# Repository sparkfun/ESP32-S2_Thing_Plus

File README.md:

SparkFun ESP32-S2 Thing Plus
========================================

[*SparkFun ESP32-S2 Thing Plus (WRL-17381)*](https://www.sparkfun.com/products/17743)

The [SparkFun ESP32-S2 Thing Plus](https://www.sparkfun.com/products/17743) is a comprehensive development platform for [Espressif's ESP32](https://espressif.com/en/products/hardware/esp32/overview). This board has the ESP32-S2-WROOM (4MB) version of the module. The new ESP32-S2 module addresses the [security flaws](https://www.espressif.com/en/news/ESP32_FIA_Analysis) in the original ESP32. While the ESP32-S2 does include improved security features, it lacks the Bluetooth capabilities of the original ESP32 module. The ESP32-S2 Thing Plus includes a Qwiic adapter, LiPo battery JST connector, and 21 I/O pins.

Repository Contents
-------------------

* **/Hardware** - Eagle design files (.brd, .sch)
* **/Hardware/Production** - Production panel files (gerbers, .brd)

Documentation
--------------
* **[Hookup Guide](https://learn.sparkfun.com/tutorials/1660)** - Basic hookup guide for the ESP32-S2 Thing Plus.
* **[SparkFun Graphical Datasheets](https://github.com/sparkfun/Graphical_Datasheets)** -Graphical Datasheets for various SparkFun products.

Product Versions
----------------
* [WRL-17743](https://www.sparkfun.com/products/17743)- v1.0, Initial Release

License Information
-------------------

This product is _**open source**_! 

Please review the LICENSE.md file for license information. 

If you have any questions or concerns on licensing, please contact technical support on our [SparkFun forums](https://forum.sparkfun.com/viewforum.php?f=152).

Distributed as-is; no warranty is given.

- Your friends at SparkFun.

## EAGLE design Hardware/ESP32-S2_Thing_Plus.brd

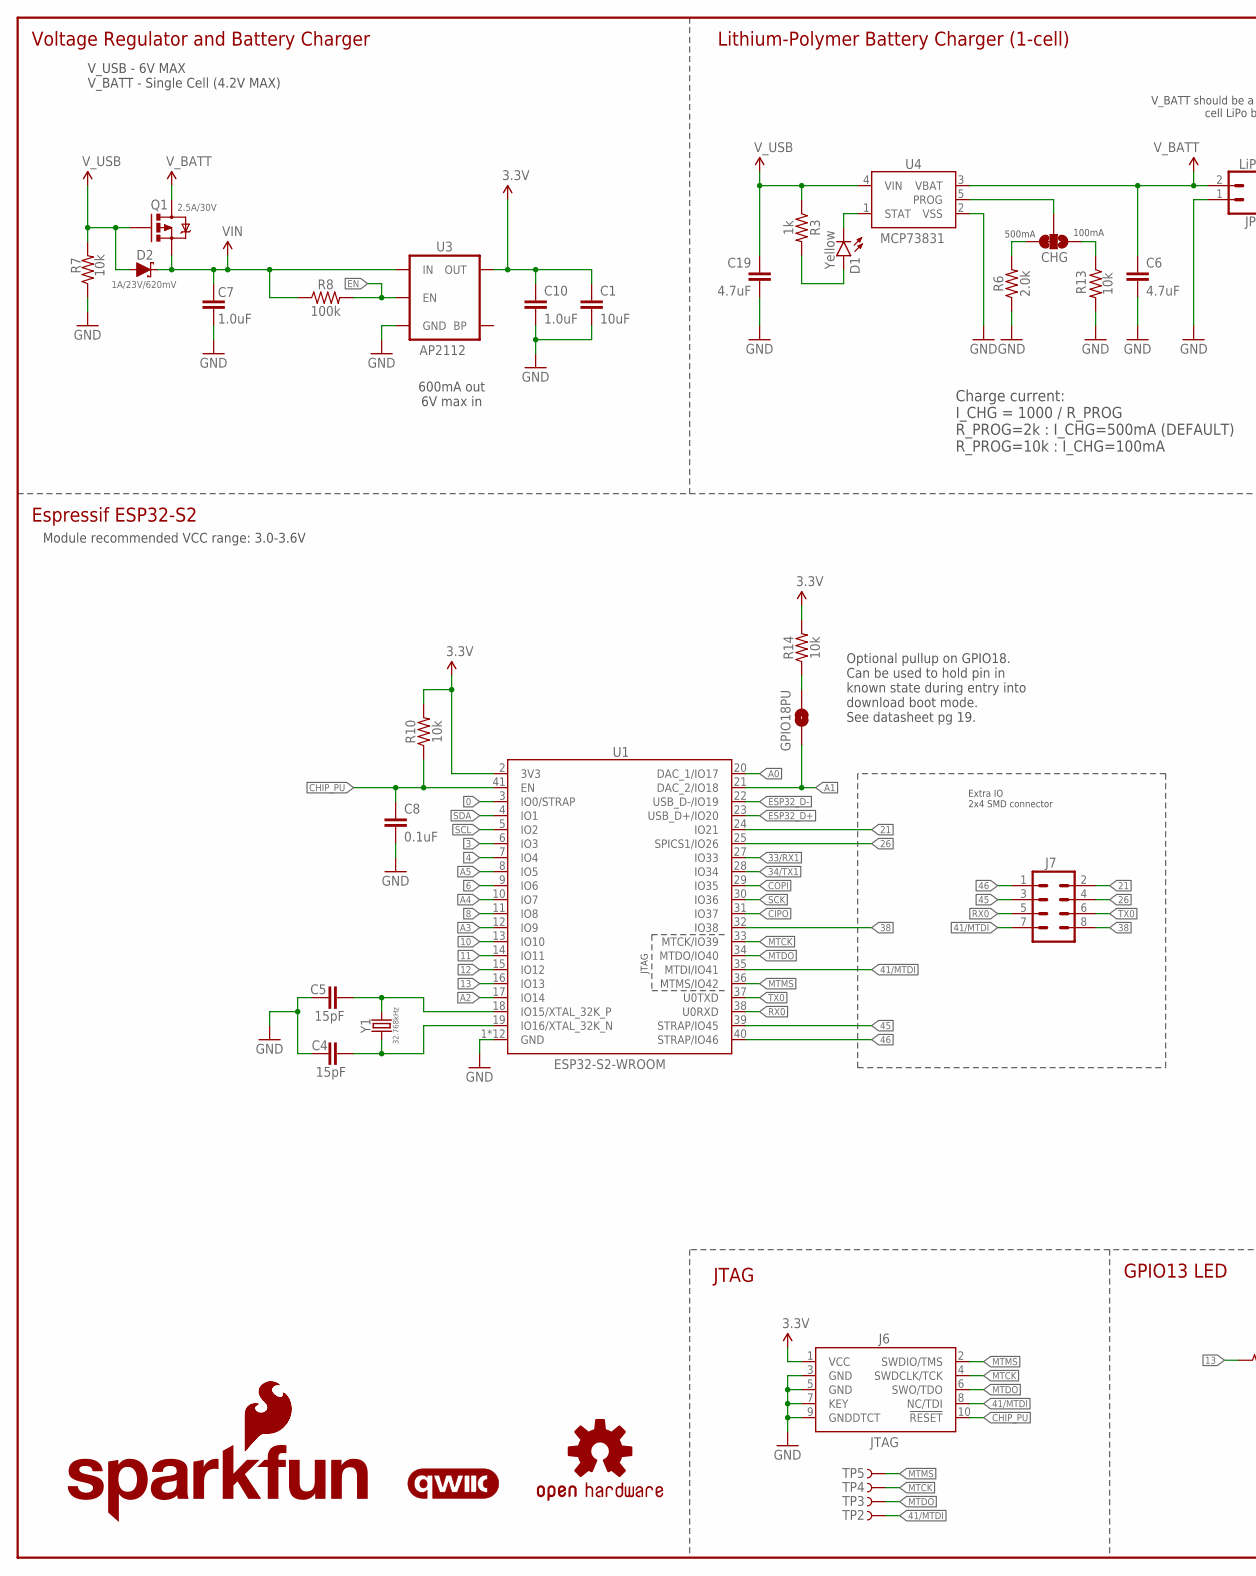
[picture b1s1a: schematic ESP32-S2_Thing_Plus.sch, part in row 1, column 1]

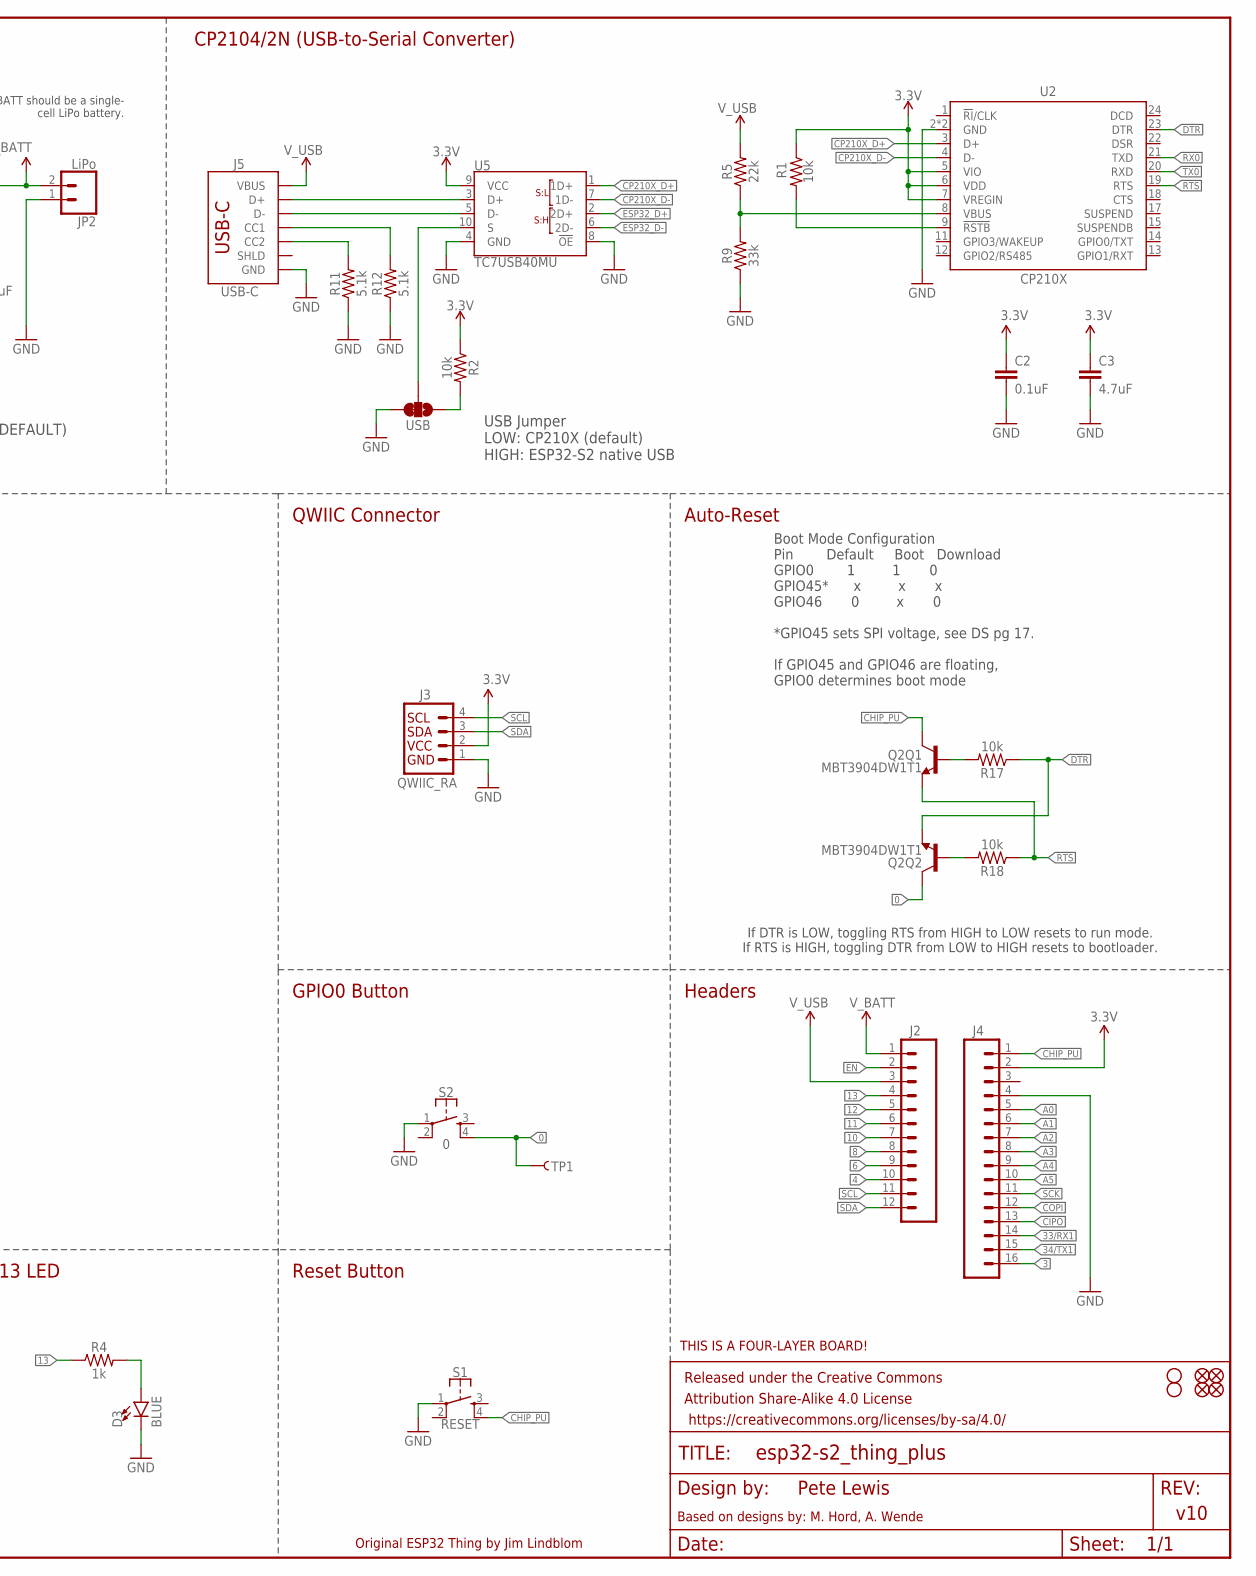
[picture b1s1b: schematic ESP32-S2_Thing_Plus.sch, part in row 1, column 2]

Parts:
C1: 10uF; 0402-TIGHT
C2, C8: 0.1uF; 0402-TIGHT
C3, C6, C19: 4.7uF; 0402-TIGHT
C4, C5: 15pF; 0402-TIGHT
C7, C10: 1.0uF; 0402-TIGHT
CHG: JUMPER-SMT_3_1-NC_TRACE_SILK; SMT-JUMPER_3_1-NC_TRACE_SILK
D1: Yellow; LED-0603
D2: 1A/23V/620mV; SOD-323
D3: BLUE; LED-0603
FD1, FD2, FD3, FD4: FIDUCIALUFIDUCIAL; FIDUCIAL-MICRO
FRAME1: FRAME-LEDGER; CREATIVE_COMMONS
GPIO18PU: JUMPER-SMT_2_NO_SILK; SMT-JUMPER_2_NO_SILK
H1, H2: STAND-OFF
J2: CONN_12SM_SQ_NO_SILK; 1X12_SM_SQ_NOSILK
J3: QWIIC_RA; JST04_1MM_RA
J4: CONN_161X16_SM_SQ_NOSILK; 1X16_SM_SQ_NOSILK
J5: USB-C; USB-C-16P-4LAYER-ISOLATED
J6: JTAG; 2X5-PTH-1.27MM-NO_SILK
J7: CONN_04X2_SMT_NO_POSTS_NS; 2X4_SMT_NO_POSTS_NS
JP2: LiPo; JST-2-SMD
LOGO1: SFE_LOGO_FLAME.1_INCH; SFE_LOGO_FLAME_.1
LOGO2: OSHW-LOGOMINI; OSHW-LOGO-MINI
LOGO3: SFE_LOGO_NAME_FLAME.1_INCH; SFE_LOGO_NAME_FLAME_.1
LOGO4: FOUR_LAYER_WARNING
LOGO6: QWIIC_LOGO_4MM; QWIIC_4MM
Q1: 2.5A/30V; SOT23-3@1
Q2: MBT3904DW1T1; SC70-6
R1, R2, R7, R10, R13, R14, R17, R18: 10k; 0402-TIGHT
R3, R4: 1k; 0402-TIGHT
R5: 22k; 0402-TIGHT
R6: 2.0k; 0603
R8: 100k; 0402-TIGHT
R9: 33k; 0402-TIGHT
R11, R12: 5.1k; 0402-TIGHT
S1: RESET; TACTILE_SWITCH_SMD_4.6X2.8MM
S2: 0; TACTILE_SWITCH_SMD_4.6X2.8MM
TP1: TEST-POINTTP_15TH_THRU; TP_15TH
TP2, TP3, TP4, TP5: TEST-POINT3X4; PAD.03X.04
U1: ESP32-S2-WROOM
U2: CP210X; QFN24
U3: AP2112; SOT23-5
U4: MCP73831; SOT23-5
U5: TC7USB40MU; UQFN10
USB: JUMPER-SMT_3_1-NC_TRACE_SILK; SMT-JUMPER_3_1-NC_TRACE_SILK
Y1: 32.768kHz; CRYSTAL-SMD-3.2X1.5MM

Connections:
0: Q2.6 (C), S2.4, TP1.P$1, U1.3 (IO0/STRAP)
3: J4.16, U1.6 (IO3)
3.3V: C1.1, C2.1, C3.1, C10.1, J3.2, J4.2, J6.1 (VCC), R1.1, R2.1, R10.2, R14.2, U1.2 (3V3), U2.5 (VIO), U2.6 (VDD), U2.7 (VREGIN), U3.5 (OUT), U5.9 (VCC)
4: J2.10, U1.7 (IO4)
6: J2.9, U1.9 (IO6)
8: J2.8, U1.11 (IO8)
10: J2.7, U1.13 (IO10)
11: J2.6, U1.14 (IO11)
12: J2.5, U1.15 (IO12)
13: J2.4, R4.1, U1.16 (IO13)
21: J7.2, U1.24 (IO21)
26: J7.4, U1.25 (SPICS1/IO26)
33/RX1: J4.14, U1.27 (IO33)
34/TX1: J4.15, U1.28 (IO34)
38: J7.8, U1.32 (IO38)
41/MTDI: J6.8 (NC/TDI), J7.7, TP2.P$1, U1.35 (MTDI/IO41)
45: J7.3, U1.39 (STRAP/IO45)
46: J7.1, U1.40 (STRAP/IO46)
A0: J4.5, U1.20 (DAC_1/IO17)
A1: GPIO18PU.1, J4.6, U1.21 (DAC_2/IO18)
A2: J4.7, U1.17 (IO14)
A3: J4.8, U1.12 (IO9)
A4: J4.9, U1.10 (IO7)
A5: J4.10, U1.8 (IO5)
CC1: J5.A5 (CC1), R12.2
CC2: J5.B5 (CC2), R11.2
CHG: D1.C, U4.1 (STAT)
CHIP_PU: C8.1, J4.1, J6.10 (!RESET), Q2.3 (C), R10.1, S1.4, U1.41 (EN)
CIPO: J4.13, U1.31 (IO37)
COPI: J4.12, U1.29 (IO35)
CP210X_D+: U2.3 (D+), U5.1 (1D+)
CP210X_D-: U2.4 (D-), U5.7 (1D-)
DTR: Q2.1 (E), R17.1, U2.23 (DTR)
EN: J2.2, R8.2, U3.3 (EN)
ESP32_D+: U1.23 (USB_D+/IO20), U5.2 (2D+)
ESP32_D-: U1.22 (USB_D-/IO19), U5.6 (2D-)
GND: C1.2, C2.2, C3.2, C4.1, C5.1, C6.2, C7.2, C8.2, C10.2, C19.2, D3.C, J3.1, J4.4, J5.GND, J5.GND2 (GND), J6.3 (GND), J6.5 (GND), J6.7 (KEY), J6.9 (GNDDTCT), JP2.1 (2), R6.1, R7.1, R9.1, R11.1, R12.1, R13.2, S1.1, S2.1, U1.1 (GND), U1.26 (GND), U1.42 (GND), U1.GNDEP0 (GND), U1.GNDEP1 (GND), U1.GNDEP2 (GND), U1.GNDEP3 (GND), U1.GNDEP4 (GND), U1.GNDEP5 (GND), U1.GNDEP6 (GND), U1.GNDEP7 (GND), U1.GNDEP8 (GND), U2.2 (GND), U2.PAD (GND), U3.2 (GND), U4.2 (VSS), U5.4 (GND), U5.8 (!OE!), USB.3
MTCK: J6.4 (SWDCLK/TCK), TP4.P$1, U1.33 (MTCK/IO39)
MTDO: J6.6 (SWO/TDO), TP3.P$1, U1.34 (MTDO/IO40)
MTMS: J6.2 (SWDIO/TMS), TP5.P$1, U1.36 (MTMS/IO42)
unnamed: R1.2, U2.9 (!RSTB)
unnamed: D3.A, R4.2
unnamed: J5.A6 (D+), J5.B6 (D+), U5.3 (D+)
unnamed: R5.1, R9.2, U2.8 (VBUS)
unnamed: J5.A7 (D-), J5.B7 (D-), U5.5 (D-)
unnamed: R2.2, USB.1
unnamed: C5.2, U1.18 (IO15/XTAL_32K_P), Y1.P$2 (2)
unnamed: C4.2, U1.19 (IO16/XTAL_32K_N), Y1.P$1 (1)
unnamed: CHG.2, U4.5 (PROG)
unnamed: Q2.5 (B), R17.2
unnamed: CHG.1, R13.1
unnamed: Q2.2 (B), R18.2
unnamed: CHG.3, R6.2
unnamed: GPIO18PU.2, R14.1
unnamed: D1.A, R3.2
RTS: Q2.4 (E), R18.1, U2.19 (RTS)
RX0: J7.5, U1.38 (U0RXD), U2.21 (TXD)
SCK: J4.11, U1.30 (IO36)
SCL: J2.11, J3.4, U1.5 (IO2)
SDA: J2.12, J3.3, U1.4 (IO1)
TX0: J7.6, U1.37 (U0TXD), U2.20 (RXD)
USB_SEL: U5.10 (S), USB.2
VIN: C7.1, D2.C, Q1.2 (S), R8.1, U3.1 (IN)
V_BATT: C6.1, J2.1, JP2.2 (1), Q1.3 (D), U4.3 (VBAT)
V_USB: C19.1, D2.A, J2.3, J5.VBUS1 (VBUS), J5.VBUS2 (VBUS), Q1.1 (G), R3.1, R5.2, R7.2, U4.4 (VIN)

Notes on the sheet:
Boot Mode Configuration Pin Default Boot Download GPIO0 1 1 0 GPIO45* x x x GPIO46 0 x 0 *GPIO45 sets SPI voltage, see DS pg 17. If GPIO45 and GPIO46 are floating, GPIO0 determines boot mode
CP2104/2N (USB-to-Serial Converter)
V_BATT should be a single- cell LiPo battery.
Charge current: I_CHG = 1000 / R_PROG R_PROG=2k : I_CHG=500mA (DEFAULT) R_PROG=10k : I_CHG=100mA
Voltage Regulator and Battery Charger
Lithium-Polymer Battery Charger (1-cell)
600mA out 6V max in
Auto-Reset
Espressif ESP32-S2
Reset Button
Headers
v10
Original ESP32 Thing by Jim Lindblom
If DTR is LOW, toggling RTS from HIGH to LOW resets to run mode. If RTS is HIGH, toggling DTR from LOW to HIGH resets to bootloader.
QWIIC Connector
Pete Lewis
GPIO13 LED
GPIO0 Button
Based on designs by: M. Hord, A. Wende
V_USB - 6V MAX V_BATT - Single Cell (4.2V MAX)
100mA
500mA
Extra IO 2x4 SMD connector
JTAG
Module recommended VCC range: 3.0-3.6V
USB Jumper LOW: CP210X (default) HIGH: ESP32-S2 native USB
Optional pullup on GPIO18. Can be used to hold pin in known state during entry into download boot mode. See datasheet pg 19.

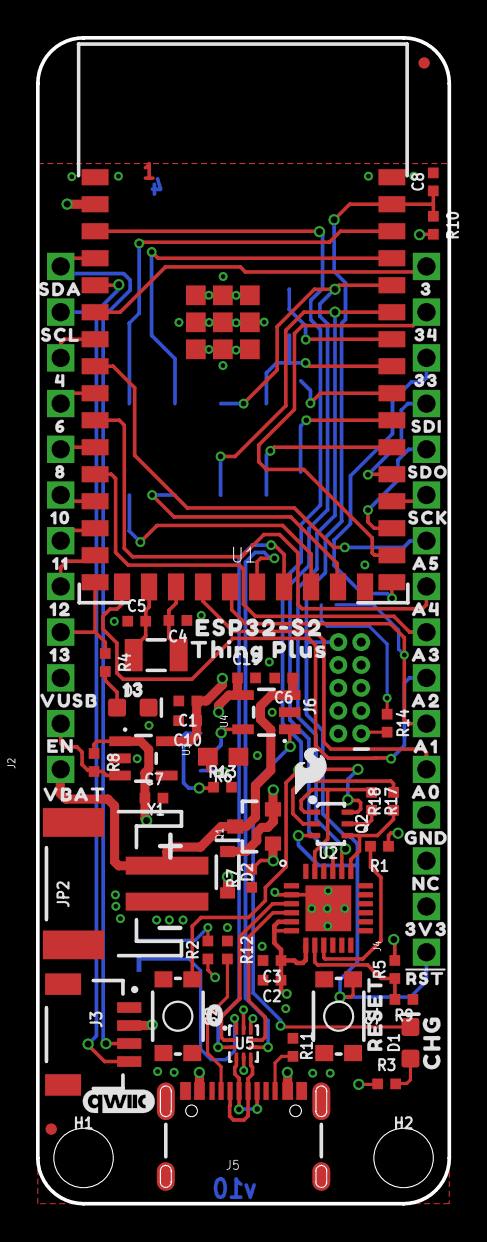
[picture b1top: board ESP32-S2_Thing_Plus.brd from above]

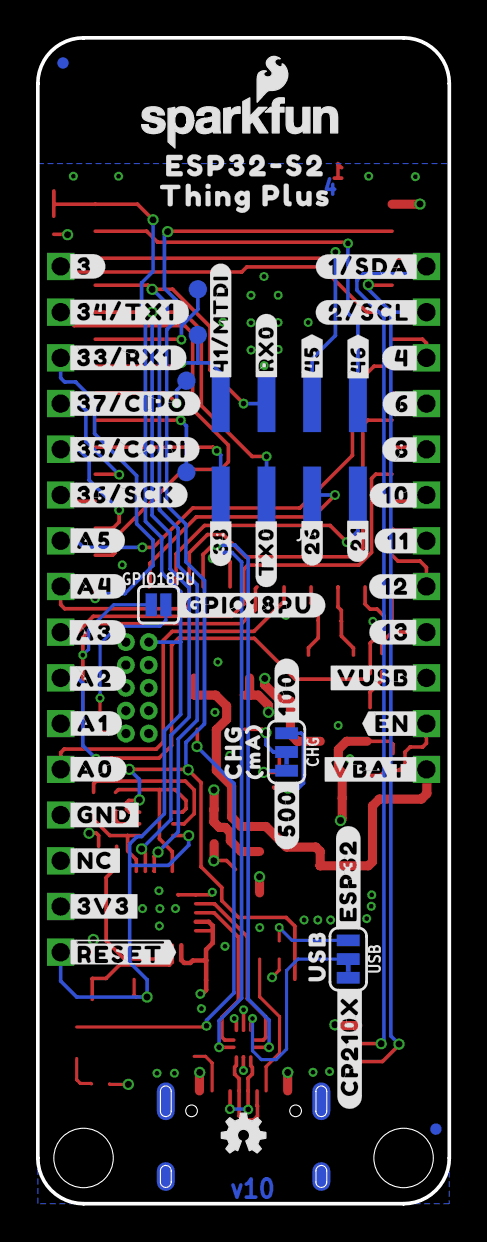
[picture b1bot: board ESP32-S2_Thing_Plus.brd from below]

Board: 4 copper layers, 22.9 x 64.8 mm, 147 parts (58 on the bottom side), 65 nets.

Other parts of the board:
U$1: #CP210X#0
U$2: SDI0
U$3, U$78: CHG0
U$4: #500#0
U$5: ESP32#S20
U$6: SDO0
U$7: #RST#0
U$8: #46#0
U$9: #ESP32#0
U$10: #45#0
U$11: MA0
U$12: #A5#0
U$14: USB0
U$15: 110
U$16: #GPIO18PU#0
U$17: 100
U$18: 80
U$19: #A4#0
U$20: 60
U$21: #A2#0
U$22: #A3#0
U$23: 40
U$24: 330
U$25: SDA0
U$26: SCL0
U$28: #A0#0
U$29: 340
U$30: 30
U$31: #36#SCK#0
U$32: #GND#0
U$33: #35#COPI#0
U$34: #37#CIPO#0
U$35: #33#RX1#0
U$36: #34#TX1#0
U$37: #3#0
U$38: #41#MTDI#0
U$39: #12#0
U$40: #13#0
U$41: #VUSB#0
U$42: #VBAT#0
U$43: #EN#0
U$44: #NC#0
U$45: #3V3#0
U$46: ##RESET##0
U$47: #11#0
U$48: #6#0
U$49: #8#0
U$50: #10#0
U$51: #4#0
U$52: #1#SDA#0
U$53: #2#SCL#0
U$54: #21#0
U$55: #26#0
U$56: #TX0#0
U$57: #38#0
U$58: #RX0#0
U$59: ORDERING_INSTRUCTIONS
U$60: #100#0
U$61: THING_PLUS0
U$62: THING_PLUS_0
U$63: ESP32#S2_0
U$64: #A1#0
U$72: 120
U$73, U$74: 130
U$75: VUSB0
U$76: EN0
U$77: VBAT0
U$79: RESET0
U$81: 3V30
U$82: NC0
U$83: GND0
U$84: A00
U$85: A10
U$86: A20
U$87: A30
U$88: A40
U$89: A50
U$90: SCK0
U$96: 00

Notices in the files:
parts and their libraries:
SparkFun-Resistors: Licensing: Creative Commons ShareAlike 4.0 International - https://creativecommons.org/licenses/by-sa/4.0
SparkFun-Aesthetics: Released under the Creative Commons Attribution Share-Alike 4.0 License
SparkFun-Aesthetics: https://creativecommons.org/licenses/by-sa/4.0
